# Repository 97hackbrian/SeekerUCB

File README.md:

# SeekerUCB
This is the official repository about the team of UCB who participate in the minesweeper competition.

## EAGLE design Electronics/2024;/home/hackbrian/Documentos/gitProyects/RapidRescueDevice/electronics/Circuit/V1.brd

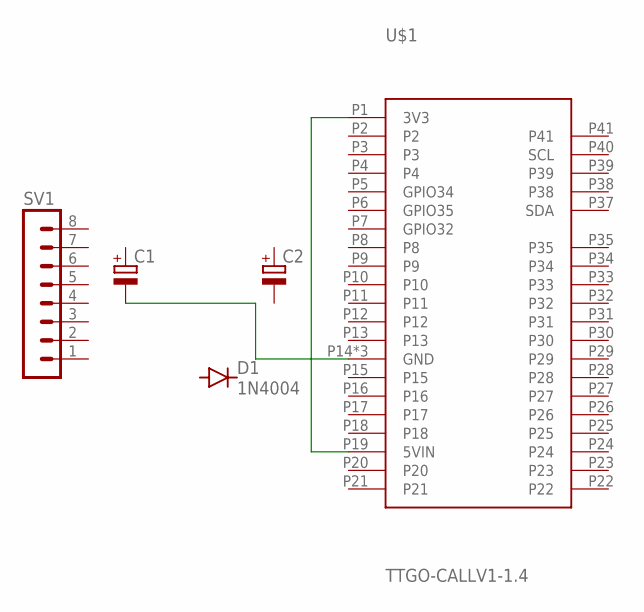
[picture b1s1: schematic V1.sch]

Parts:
C1, C2: CPOL-EUE3.5-8; E3,5-8
D1: 1N4004; DO41-10
SV1: MA08-1
U$1: TTGO-CALLV1-1.4; TTGO-CALLV11.4

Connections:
unnamed: U$1.P1 (3V3), U$1.P19 (5VIN)
unnamed: C1.-, U$1.P14 (GND), U$1.P36 (GND), U$1.P42 (GND)

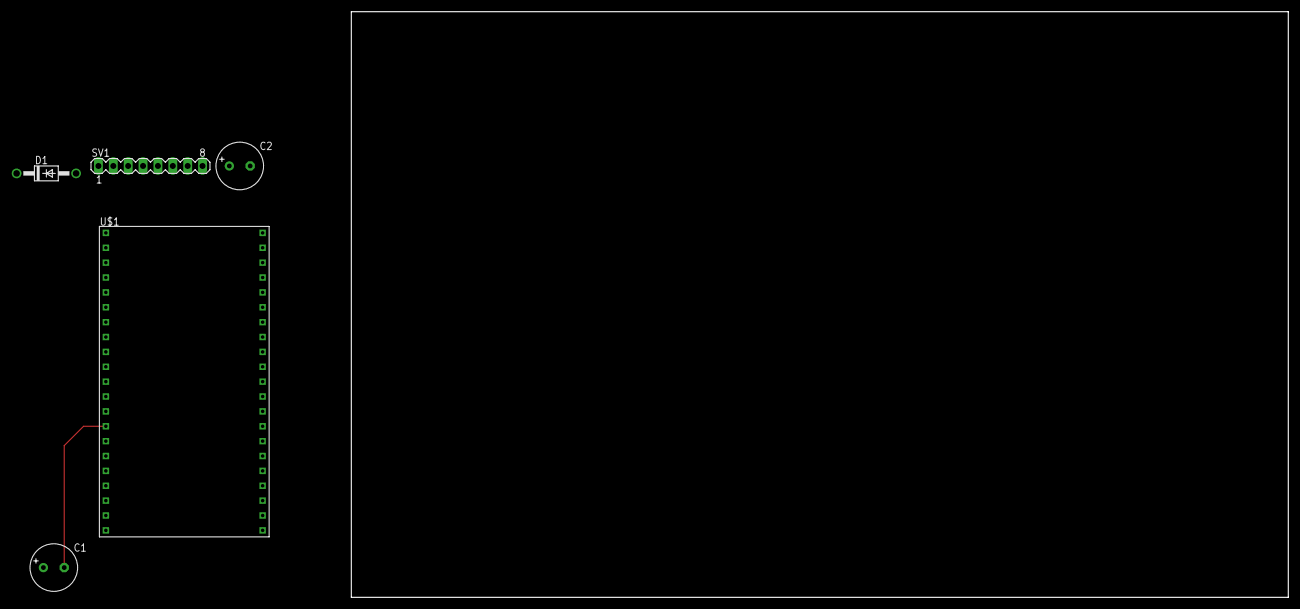
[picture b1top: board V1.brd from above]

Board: 2 copper layers, 160.0 x 100.0 mm, 5 parts (0 on the bottom side), 2 nets.

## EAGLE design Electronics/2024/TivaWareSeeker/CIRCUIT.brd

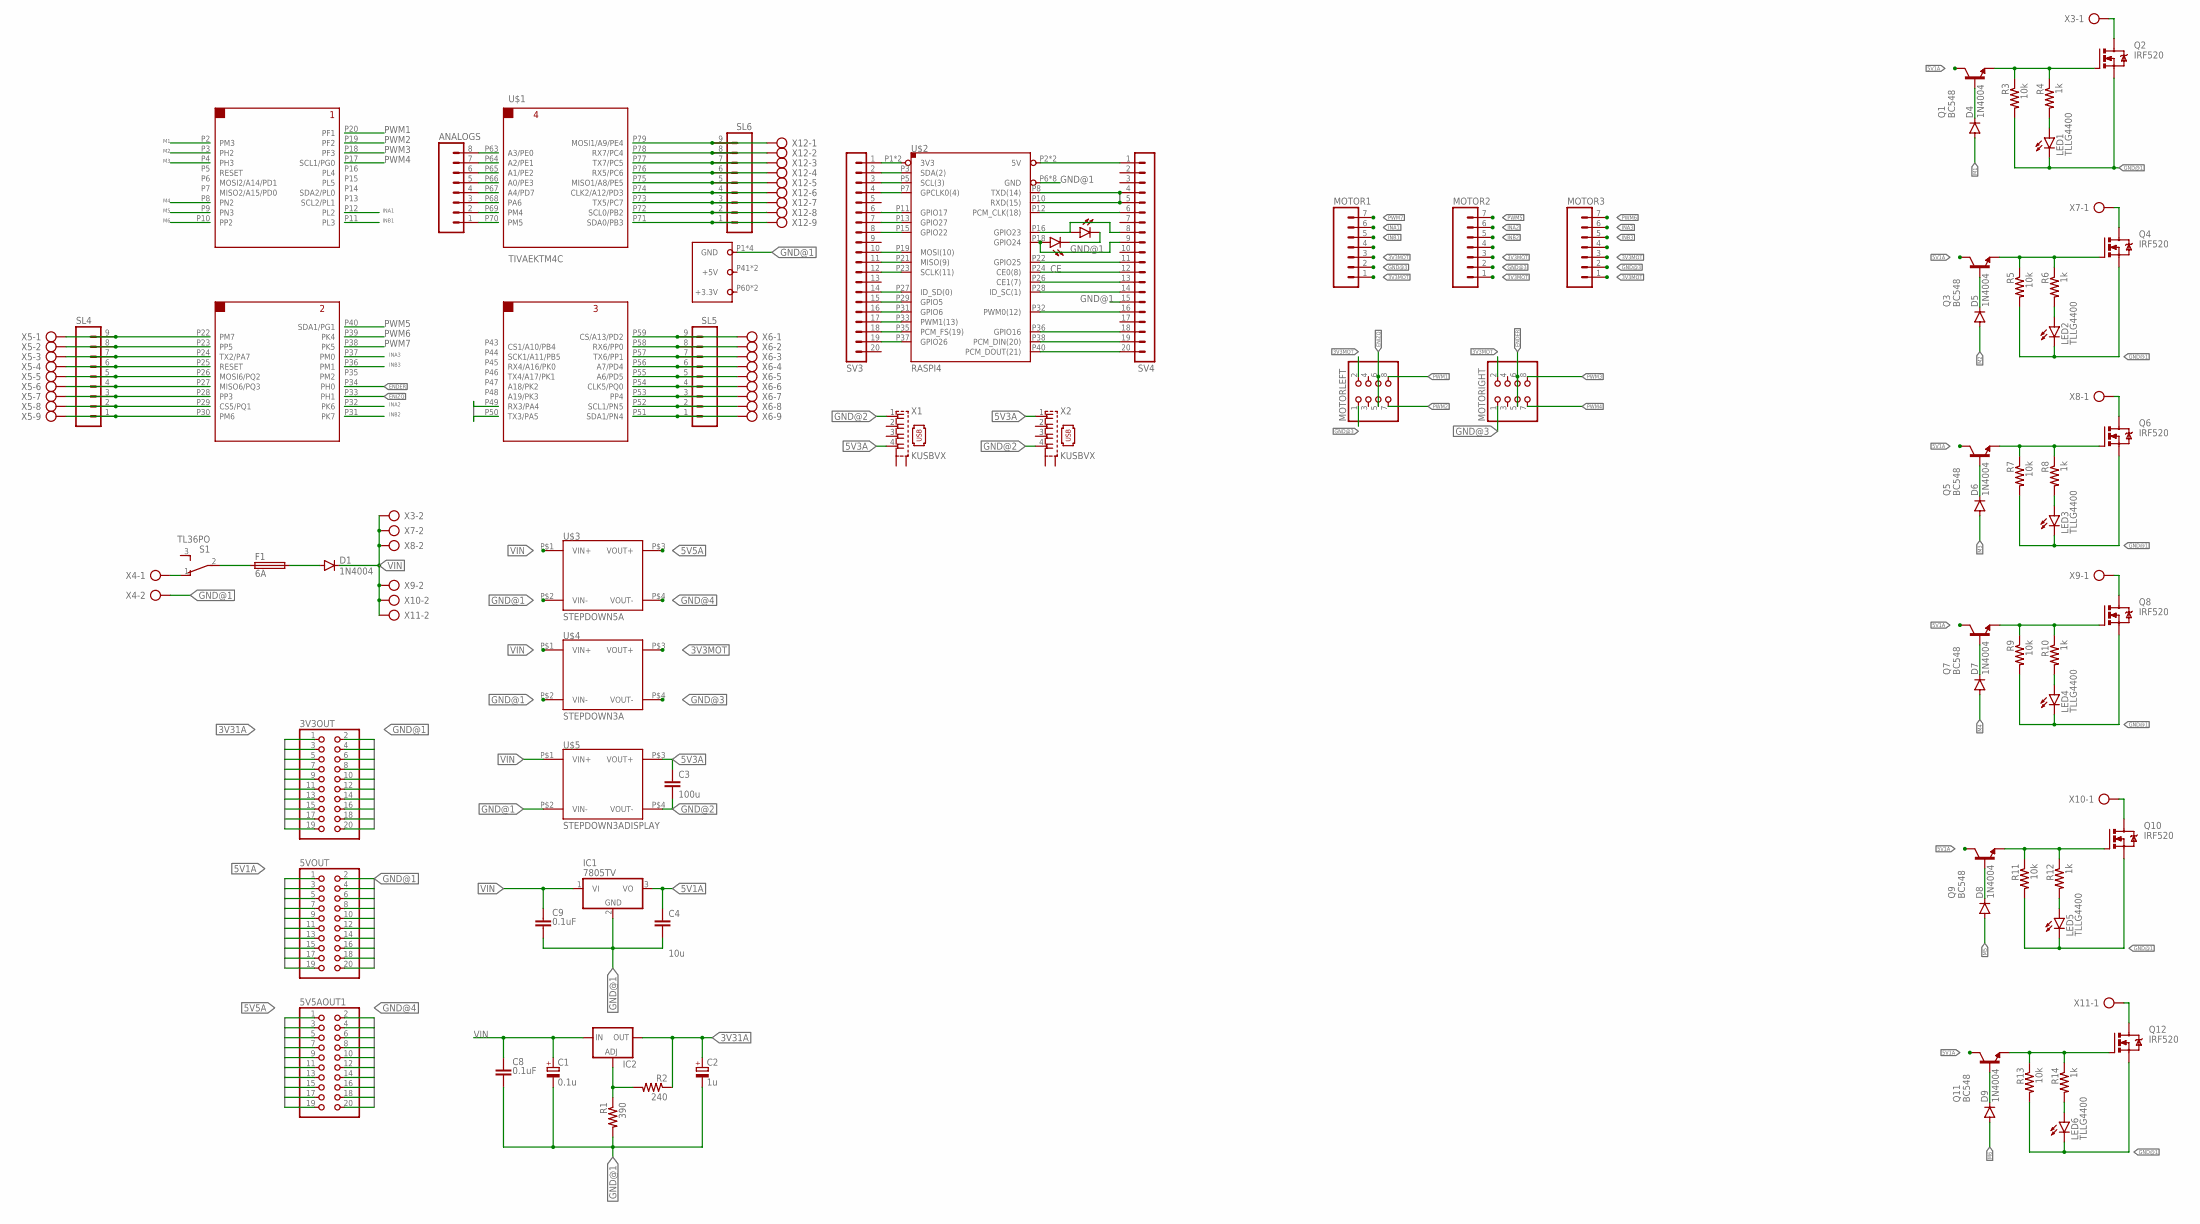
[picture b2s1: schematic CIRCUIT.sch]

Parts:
3V3OUT, 5V5AOUT1, 5VOUT: PINHD-2X10; 2X10
ANALOGS: MA08; 08PA
C1: 0.1u; E5-10,5
C2: 1u; E5-10,5
C3: 100u; C025-024X044
C4: 10u; C025-024X044
C8, C9: 0.1uF; C075-052X106
D1, D4, D5, D6, D7, D8, D9: 1N4004; DO41-10
D2, D3: SFH482
F1: 6A; SHK20L
IC1: 7805TV; TO220V
IC2: LM317TL; 317TL
LED1, LED2, LED3, LED4, LED5, LED6: TLLG4400; LED3MM
MOTOR1, MOTOR2, MOTOR3: MA07; 07PA
MOTORIGHT: PINHD-2X4; 2X04
MOTORLEFT: PINHD-2X4; 2X04
Q1, Q3, Q5, Q7, Q9, Q11: BC548; TO92-EBC
Q2, Q4, Q6, Q8, Q10, Q12: IRF520; TO220BV
R1: 390; 0207/10
R2: 240; 0207/10
R3, R5, R7, R9, R11, R13: 10k; 0207/10
R4, R6, R8, R10, R12, R14: 1k; 0207/10
S1: TL36PO; TL3XPO
SL4, SL5, SL6: M09; 09P
SV3, SV4: MA20-1
U$1: TIVAEKTM4C; TIVAPINESPCB
U$2: RASPI4; CONN2-SIL40
U$3: STEPDOWN5A; REGULADORSTEP-DOWN5ACURRENT
U$4: STEPDOWN3A; REGULADORSTEP-DOWN3A
U$5: STEPDOWN3ADISPLAY; REGULADORWITHDISPLAY
X1, X2: KUSBVX
X3, X4, X7, X8, X9, X10, X11: AK300/2
X5, X6, X12: AK300/9

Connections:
3V3MOT: MOTOR1.1, MOTOR1.3, MOTOR2.1, MOTOR2.3, MOTOR3.1, MOTOR3.3, MOTORIGHT.2, MOTORLEFT.2, U$4.P$3 (VOUT+)
3V31A: 3V3OUT.1, 3V3OUT.3, 3V3OUT.5, 3V3OUT.7, 3V3OUT.9, 3V3OUT.11, 3V3OUT.13, 3V3OUT.15, 3V3OUT.17, 3V3OUT.19, C2.+, IC2.2 (OUT), R2.1
5V1A: 5VOUT.1, 5VOUT.3, 5VOUT.5, 5VOUT.7, 5VOUT.9, 5VOUT.11, 5VOUT.13, 5VOUT.15, 5VOUT.17, 5VOUT.19, C4.1, IC1.3 (VO), Q1.C, Q3.C, Q5.C, Q7.C, Q9.C, Q11.C
5V3A: C3.1, U$5.P$3 (VOUT+), X1.4, X2.1
5V5A: 5V5AOUT1.1, 5V5AOUT1.3, 5V5AOUT1.5, 5V5AOUT1.7, 5V5AOUT1.9, 5V5AOUT1.11, 5V5AOUT1.13, 5V5AOUT1.15, 5V5AOUT1.17, 5V5AOUT1.19, U$3.P$3 (VOUT+)
CE: SV4.12, U$2.P24 (CE0(8))
CLK: SV3.12, U$2.P23 (SCLK(11))
ENDER: MOTORIGHT.5, MOTORIGHT.6, U$1.P34 (PH0)
ENIZQ: MOTORLEFT.5, MOTORLEFT.6, U$1.P33 (PH1)
GND@1: 3V3OUT.2, 3V3OUT.4, 3V3OUT.6, 3V3OUT.8, 3V3OUT.10, 3V3OUT.12, 3V3OUT.14, 3V3OUT.16, 3V3OUT.18, 3V3OUT.20, 5VOUT.2, 5VOUT.4, 5VOUT.6, 5VOUT.8, 5VOUT.10, 5VOUT.12, 5VOUT.14, 5VOUT.16, 5VOUT.18, 5VOUT.20, C4.2, C9.2, D2.K (C), D3.K (C), IC1.2 (GND), LED1.K (C), LED2.K (C), LED3.K (C), LED4.K (C), LED5.K (C), LED6.K (C), Q2.S, Q4.S, Q6.S, Q8.S, Q10.S, Q12.S, R3.2, R5.2, R7.2, R9.2, R11.2, R13.2, SV4.15, U$1.P1 (GND), U$1.P21 (GND), U$1.P42 (GND), U$1.P62 (GND), U$2.P6 (GND), U$2.P9 (GND), U$2.P14 (GND), U$2.P20 (GND), U$2.P25 (GND), U$2.P30 (GND), U$2.P34 (GND), U$2.P39 (GND), U$3.P$2 (VIN-), U$4.P$2 (VIN-), U$5.P$2 (VIN-), X4.2
GND@2: C3.2, U$5.P$4 (VOUT-), X1.1, X2.4
GND@3: MOTOR1.2, MOTOR2.2, MOTOR3.2, MOTORIGHT.1, MOTORLEFT.1, U$4.P$4 (VOUT-)
GND@4: 5V5AOUT1.2, 5V5AOUT1.4, 5V5AOUT1.6, 5V5AOUT1.8, 5V5AOUT1.10, 5V5AOUT1.12, 5V5AOUT1.14, 5V5AOUT1.16, 5V5AOUT1.18, 5V5AOUT1.20, U$3.P$4 (VOUT-)
INA1: MOTOR1.6, U$1.P12 (PL2)
INA2: MOTOR2.6, U$1.P32 (PK6)
INA3: MOTOR3.6, U$1.P37 (PM0)
INB1: MOTOR1.5, U$1.P11 (PL3)
INB2: MOTOR2.5, U$1.P31 (PK7)
INB3: MOTOR3.5, U$1.P36 (PM1)
M1: D4.A, U$1.P2 (PM3)
M2: D5.A, U$1.P3 (PH2)
M3: D6.A, U$1.P4 (PH3)
M4: D7.A, U$1.P8 (PN2)
M5: D8.A, U$1.P9 (PN3)
M6: D9.A, U$1.P10 (PP2)
MISO: SV3.10, SV3.11, U$2.P19 (MOSI(10)), U$2.P21 (MISO(9))
unnamed: S1.1 (O), X4.1
unnamed: F1.1A, S1.2
unnamed: IC2.1 (ADJ), R1.1, R2.2
unnamed: SV3.1, U$2.P1 (3V3), U$2.P17 (3V3)
unnamed: C1.-, C2.-, C8.2, R1.2
unnamed: SV3.2, U$2.P3 (SDA(2))
unnamed: SV3.3, U$2.P5 (SCL(3))
unnamed: SV3.4, U$2.P7 (GPCLK0(4))
unnamed: SV3.6, U$2.P11 (GPIO17)
unnamed: SV3.7, U$2.P13 (GPIO27)
unnamed: SV3.8, U$2.P15 (GPIO22)
unnamed: D1.A, F1.2A
unnamed: SV3.14, U$2.P27 (ID_SD(0))
unnamed: SV3.15, U$2.P29 (GPIO5)
unnamed: SV3.16, U$2.P31 (GPIO6)
unnamed: SV3.17, U$2.P33 (PWM1(13))
unnamed: SV3.18, U$2.P35 (PCM_FS(19))
unnamed: SV3.19, U$2.P37 (GPIO26)
unnamed: SV4.1, U$2.P2 (5V), U$2.P4 (5V)
unnamed: D4.C, Q1.B
unnamed: SV4.6, U$2.P12 (PCM_CLK(18))
unnamed: D3.A, SV4.9, U$2.P18 (GPIO24)
unnamed: Q1.E, Q2.G, R3.1, R4.1
unnamed: SV4.11, U$2.P22 (GPIO25)
unnamed: LED1.A, R4.2
unnamed: D5.C, Q3.B
unnamed: SV4.13, U$2.P26 (CE1(7))
unnamed: SV4.14, U$2.P28 (ID_SC(1))
unnamed: SV4.16, U$2.P32 (PWM0(12))
unnamed: SV4.18, U$2.P36 (GPIO16)
unnamed: SV4.19, U$2.P38 (PCM_DIN(20))
unnamed: SV4.20, U$2.P40 (PCM_DOUT(21))
unnamed: D2.A, SV4.8, U$2.P16 (GPIO23)
unnamed: Q2.D, X3.1
unnamed: SL4.9, U$1.P22 (PM7), X5.1
unnamed: Q3.E, Q4.G, R5.1, R6.1
unnamed: LED2.A, R6.2
unnamed: Q4.D, X7.1
unnamed: D6.C, Q5.B
unnamed: Q5.E, Q6.G, R7.1, R8.1
unnamed: LED3.A, R8.2
unnamed: Q6.D, X8.1
unnamed: D7.C, Q7.B
unnamed: Q7.E, Q8.G, R9.1, R10.1
unnamed: LED4.A, R10.2
unnamed: Q8.D, X9.1
unnamed: D8.C, Q9.B
unnamed: Q9.E, Q10.G, R11.1, R12.1
unnamed: LED5.A, R12.2
unnamed: Q10.D, X10.1
unnamed: D9.C, Q11.B
unnamed: Q11.E, Q12.G, R13.1, R14.1
unnamed: LED6.A, R14.2
unnamed: Q12.D, X11.1
unnamed: SL4.8, U$1.P23 (PP5), X5.2
unnamed: SL4.7, U$1.P24 (TX2/PA7), X5.3
unnamed: SL4.6, U$1.P25 (RESET), X5.4
unnamed: SL4.5, U$1.P26 (MOSI6/PQ2), X5.5
unnamed: SL4.4, U$1.P27 (MISO6/PQ3), X5.6
unnamed: SL4.3, U$1.P28 (PP3), X5.7
unnamed: SL4.2, U$1.P29 (CS5/PQ1), X5.8
unnamed: SL4.1, U$1.P30 (PM6), X5.9
unnamed: SL6.9, U$1.P79 (MOSI1/A9/PE4), X12.1
unnamed: SL6.8, U$1.P78 (RX7/PC4), X12.2
unnamed: SL6.7, U$1.P77 (TX7/PC5), X12.3
unnamed: SL6.6, U$1.P76 (RX5/PC6), X12.4
unnamed: SL6.5, U$1.P75 (MISO1/A8/PE5), X12.5
unnamed: SL6.4, U$1.P74 (CLK2/A12/PD3), X12.6
unnamed: SL6.3, U$1.P73 (TX5/PC7), X12.7
unnamed: SL6.2, U$1.P72 (SCL0/PB2), X12.8
unnamed: SL6.1, U$1.P71 (SDA0/PB3), X12.9
unnamed: SL5.9, U$1.P59 (CS/A13/PD2), X6.1
unnamed: SL5.8, U$1.P58 (RX6/PP0), X6.2
unnamed: SL5.7, U$1.P57 (TX6/PP1), X6.3
unnamed: SL5.6, U$1.P56 (A7/PD4), X6.4
unnamed: SL5.5, U$1.P55 (A6/PD5), X6.5
unnamed: SL5.4, U$1.P54 (CLK5/PQ0), X6.6
unnamed: SL5.3, U$1.P53 (PP4), X6.7
unnamed: SL5.2, U$1.P52 (SCL1/PN5), X6.8
unnamed: SL5.1, U$1.P51 (SDA1/PN4), X6.9
unnamed: ANALOGS.8, U$1.P63 (A3/PE0)
unnamed: ANALOGS.7, U$1.P64 (A2/PE1)
unnamed: ANALOGS.6, U$1.P65 (A1/PE2)
unnamed: ANALOGS.5, U$1.P66 (A0/PE3)
unnamed: ANALOGS.4, U$1.P67 (A4/PD7)
unnamed: ANALOGS.3, U$1.P68 (PA6)
unnamed: ANALOGS.2, U$1.P69 (PM4)
unnamed: ANALOGS.1, U$1.P70 (PM5)
PWM1: MOTORLEFT.8, U$1.P20 (PF1)
PWM2: MOTORLEFT.7, U$1.P19 (PF2)
PWM3: MOTORIGHT.8, U$1.P18 (PF3)
PWM4: MOTORIGHT.7, U$1.P17 (SCL1/PG0)
PWM5: MOTOR2.7, U$1.P40 (SDA1/PG1)
PWM6: MOTOR3.7, U$1.P39 (PK4)
PWM7: MOTOR1.7, U$1.P38 (PK5)
RX: SV4.5, U$2.P10 (RXD(15))
RX3: U$1.P49 (RX3/PA4)
TX: SV4.4, U$2.P8 (TXD(14))
TX3: U$1.P50 (TX3/PA5)
VIN: C1.+, C8.1, C9.1, D1.C, IC1.1 (VI), IC2.3 (IN), U$3.P$1 (VIN+), U$4.P$1 (VIN+), U$5.P$1 (VIN+), X3.2, X7.2, X8.2, X9.2, X10.2, X11.2

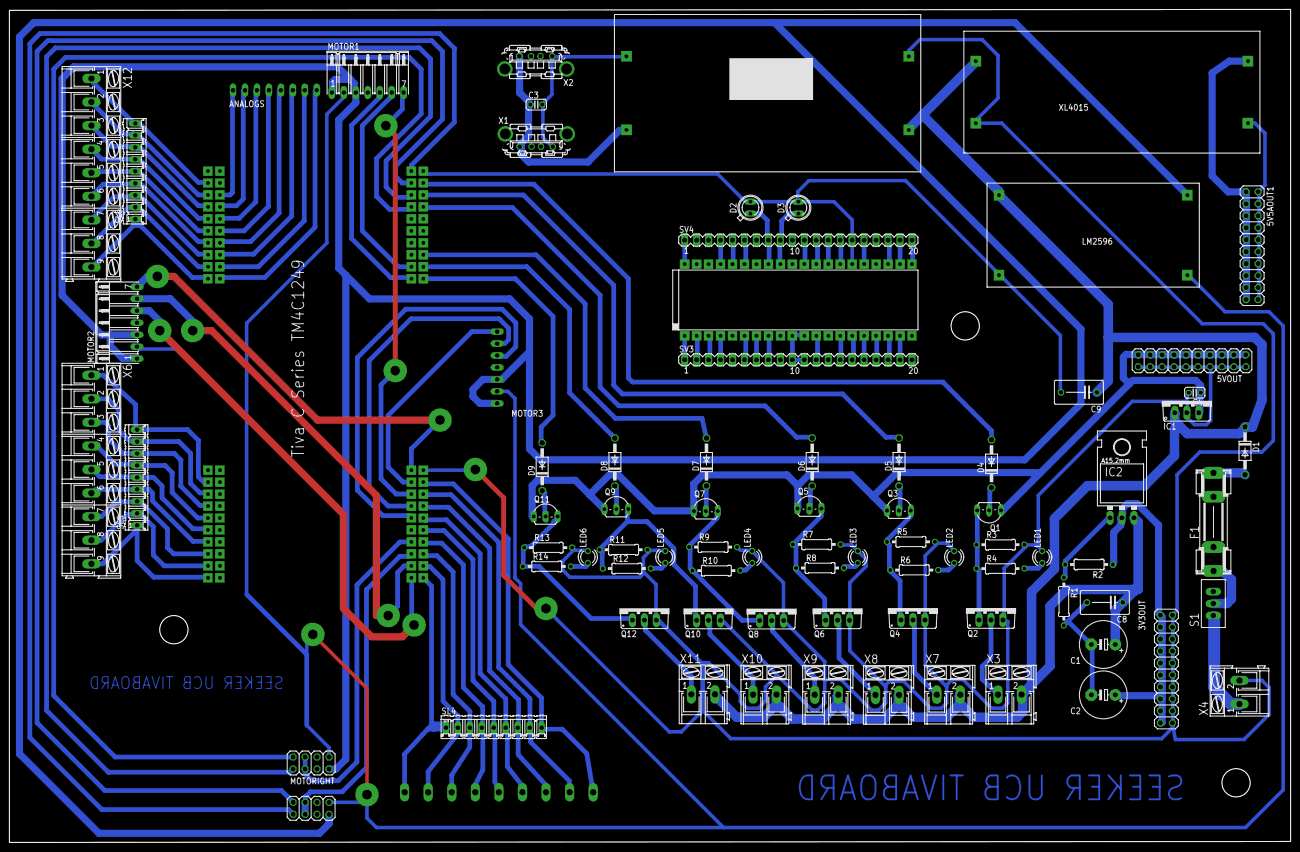
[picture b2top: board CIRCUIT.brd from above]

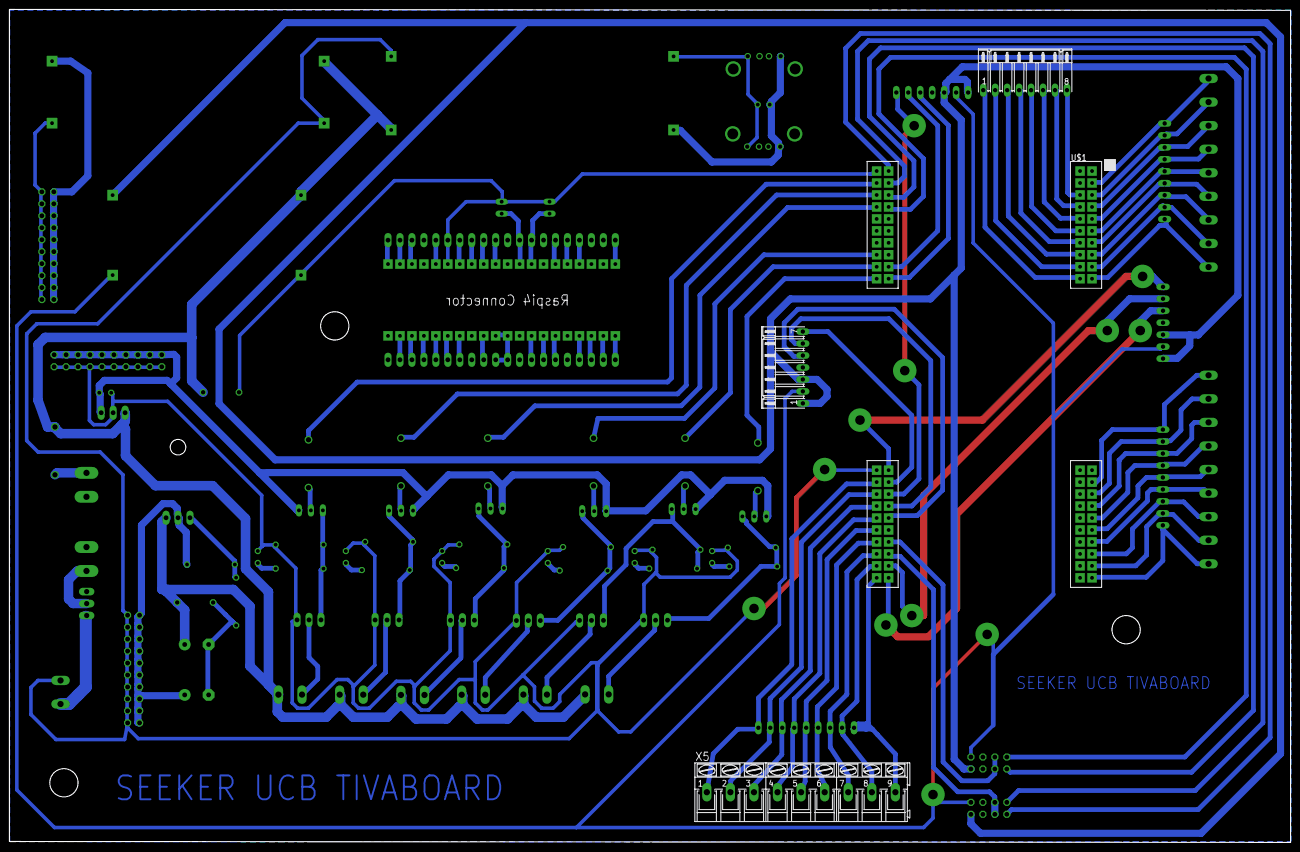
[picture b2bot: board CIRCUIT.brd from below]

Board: 2 copper layers, 272.0 x 176.8 mm, 82 parts (4 on the bottom side), 124 nets.

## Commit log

2023-07-21 Proteus8.12
2023-07-22 V2withoutRouting
2023-08-04 Fv1-LastWeek
2023-08-04 VfwihoutPCBPass1
2023-08-05 VfinaPDF
2023-08-12 MotorLib-V1
2023-08-13 Example motor
2023-08-13 motorExampleV1
2023-08-22 FAilCompile
2023-08-22 Revenge
2023-08-22 V1Revenge
2023-08-22 V1PreImplmentacion
2023-08-28 gitignore
2023-08-29 RevengeV2
2023-08-31 ExtentionsPack
2023-09-02 BeforeTarija
2023-09-04 beforeCompetition
2023-11-11 electronicsMid
2023-11-11 libraries
2023-11-13 BoardMiddle
2023-11-13 BoardMiddle without optimization and review
2023-11-13 TIvaboardV1
2023-11-20 example1
2023-11-27 Weimae
2023-12-05 RosV1
2023-12-05 fgfd
2023-12-05 ros2
2023-12-05 Ros2V1
2023-12-09 electr
